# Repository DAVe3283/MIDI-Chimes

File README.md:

# MIDI-Chimes
Software &amp; notes from retrofitting some old chimes to MIDI control

Eventually, this will contain schematics, PCB layouts, data sheets, and source
code to make everything work. I will add things as I get to them.

## Project Details

TODO: writeup project details

## Firmware

The project uses several Teensy 3.2 microcontrollers. There is a master, which
handles MIDI and the user interface. The rest are slaves, which run 10 chimes
each.

The master and slaves communicate over I2C. The master talks to a touch screen
LCD over SPI.

### Libraries

I am using the following libraries:

* [i2c_t3][] - A superior I2C library that runs quite fast on the Teensy3.
* [ILI9341_t3][] - An optimized ILI9343 SPI LCD driver library for the Teensy3.
* [ILI9341_fonts][] - Additional fonts for ILI9341_t3.
* [Adafruit_STMPE610][] - STMPE610 SPI touch screen controller library.
* [Adafruit_FT6206][] - FT6206 I2C touch screen controller library.
* [SdFat][] - SD Card + FAT file system library.
* [IniFile][] - Arduino library to parse INI files.

Some minor changes are needed to make the libraries work together for this
project.

#### Adafruit_STMPE610

The line `#include <Wire.h>` needs changed to `#include <i2c_t3.h>` or it
conflicts with the i2c_t3 library.

#### SdFat

To work right, the SdFat library needs the following settings in SdFatConfig.h:

`#define SD_SPI_CONFIGURATION 1`

This uses the Arduino SPI.h library, which is really an optimized one for the
Teensy 3.1.

`#define ENABLE_SPI_TRANSACTION 1`

This enables SPI transactions, which makes using multiple devices on the SPI bus
much nicer.

I had some issues with SdFat-beta, but I might go back and make that work,
because it does some cool stuff.

#### IniFile

In IniFile.h, `#include <SD.h>` needs changed to `#include <SdFat.h>`.

Immediately below the includes, add the following so the inline code works with
this program:

```c++
extern SdFat sd;
#define SD sd
```

## Schematics

See the "PCB & Schematic" directory, and the [PCB.md](Notes/PCB.md) file.

## License

Content in each folder may be licensed differently. Overall, I strive to use the
Unlicense, but some portions may use external libraries preventing that. Those
portions will be licensed as necessary. Data sheets and the like are provided
for reference only, and are subject to all licenses/copyright specified within.

[Adafruit_FT6206]: https://github.com/adafruit/Adafruit_FT6206_Library
[Adafruit_STMPE610]: https://github.com/adafruit/Adafruit_STMPE610
[i2c_t3]: https://github.com/nox771/i2c_t3
[ILI9341_fonts]: https://github.com/PaulStoffregen/ILI9341_fonts
[ILI9341_t3]: https://github.com/PaulStoffregen/ILI9341_t3
[SdFat]: https://github.com/greiman/SdFat
[IniFile]: https://github.com/stevemarple/IniFile

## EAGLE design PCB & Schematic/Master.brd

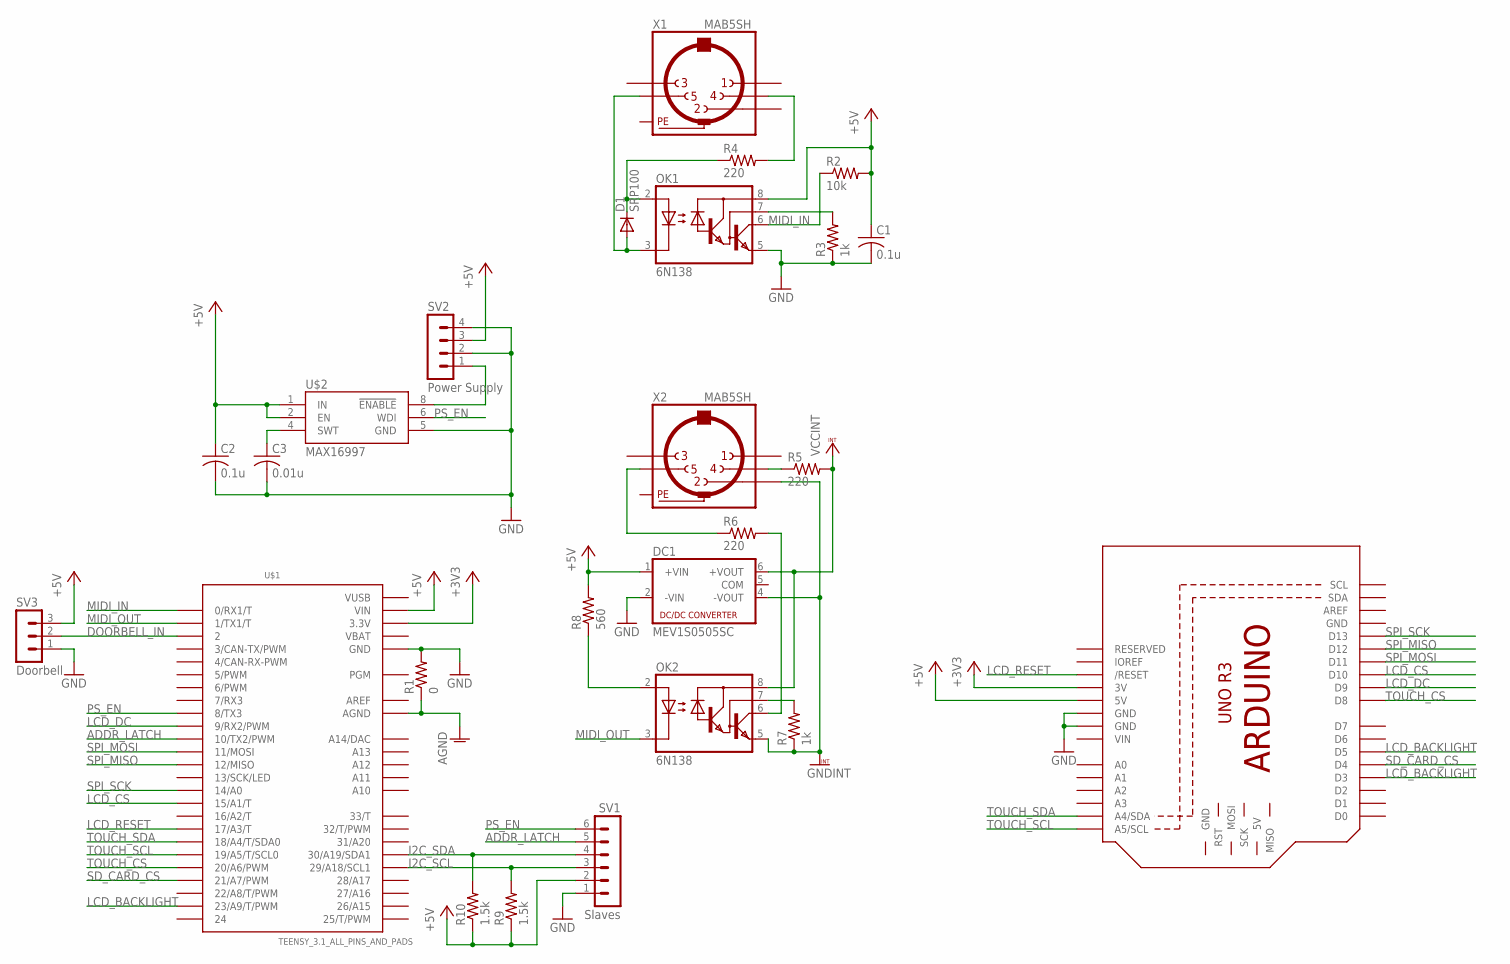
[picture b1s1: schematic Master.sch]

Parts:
C1, C2: 0.1u; C0805
C3: 0.01u; C0805
D1: SRP100; DO41-10
DC1: MEV1S0505SC; NMA
M1: ARDUINO_R3_ICSP_NODIM; ARDUINOR3_ICSP_NODIM
OK1, OK2: 6N138; DIL08
R1: 0; R0805
R2: 10k; R0805
R3, R7: 1k; R0805
R4, R5, R6: 220; R0805
R8: 560; R0805
R9, R10: 1.5k; R0805
SV1: Slaves; MA06-1
SV2: Power Supply; MA04-1
SV3: Doorbell; MA03-1
U$1: TEENSY_3.1_ALL_PINS_AND_PADS; TEENSY3_ALL_PINS_&_PADS
U$2: MAX16997; UMAX-U8-1
X1, X2: MAB5SH

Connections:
+3V3: M1.3V, U$1.3.3V, U$1.3.3V1 (3.3V), U$1.3.3V2 (3.3V)
+5V: C1.1, C2.1, DC1.1 (+VIN), M1.5V, OK1.8 (VCC), R2.2, R8.2, R9.1, R10.1, SV1.2, SV2.3, SV3.3, U$1.VIN, U$2.1 (IN), U$2.2 (EN)
ADDR_LATCH: SV1.5, U$1.10 (10/TX2/PWM)
AGND: R1.1, U$1.AGND
AREF: U$1.AREF
DOORBELL_IN: SV3.2, U$1.2
GND: C1.2, C2.2, C3.2, DC1.2 (-VIN), M1.GND, M1.GND@1 (GND), M1.GND@3 (GND), OK1.5 (GND), R1.2, R3.1, SV1.1, SV2.2, SV2.4, SV3.1, U$1.GND, U$1.GND1 (GND), U$1.GND2 (GND), U$2.5 (GND)
GNDINT: DC1.4 (-VOUT), OK2.5 (GND), R7.1, X2.2
I2C_SCL: R9.2, SV1.3, U$1.29 (29/A18/SCL1)
I2C_SDA: R10.2, SV1.4, U$1.30 (30/A19/SDA1)
LCD_BACKLIGHT: M1.D3, M1.D5, U$1.23/A9 (23/A9/T/PWM)
LCD_CS: M1.D10, U$1.15/A1 (15/A1/T)
LCD_DC: M1.D9, U$1.9 (9/RX2/PWM)
LCD_RESET: M1.RESET (/RESET), U$1.17/A3 (17/A3/T)
MIDI_IN: OK1.6 (VO), R2.1, U$1.0 (0/RX1/T)
MIDI_OUT: OK2.3 (C), U$1.1 (1/TX1/T)
unnamed: R6.1, X2.5
unnamed: OK1.7 (VB), R3.2
unnamed: D1.C, OK1.2 (A), R4.1
unnamed: R4.2, X1.4
unnamed: D1.A, OK1.3 (C), X1.5
unnamed: OK2.6 (VO), R6.2
unnamed: R5.1, X2.4
unnamed: C3.1, U$2.4 (SWT)
unnamed: OK2.2 (A), R8.1
unnamed: OK2.7 (VB), R7.2
unnamed: SV2.1, U$2.8 (!ENABLE)
PE: X1.PE, X1.PE@ (PE), X2.PE, X2.PE@ (PE)
PS_EN: SV1.6, U$1.8 (8/TX3), U$2.6 (WDI)
SD_CARD_CS: M1.D4, U$1.21/A7 (21/A7/PWM)
SPI_MISO: M1.D12, U$1.12 (12/MISO)
SPI_MOSI: M1.D11, U$1.11 (11/MOSI)
SPI_SCK: M1.D13, U$1.14/A0
TOUCH_CS: M1.D8, U$1.20/A6 (20/A6/PWM)
TOUCH_SCL: M1.A5 (A5/SCL), U$1.19/A5 (19/A5/T/SCL0)
TOUCH_SDA: M1.A4 (A4/SDA), U$1.18/A4 (18/A4/T/SDA0)
VBAT: U$1.VBAT
VCCINT: DC1.6 (+VOUT), OK2.8 (VCC), R5.2
VIN: M1.VIN
VUSB: U$1.VUSB

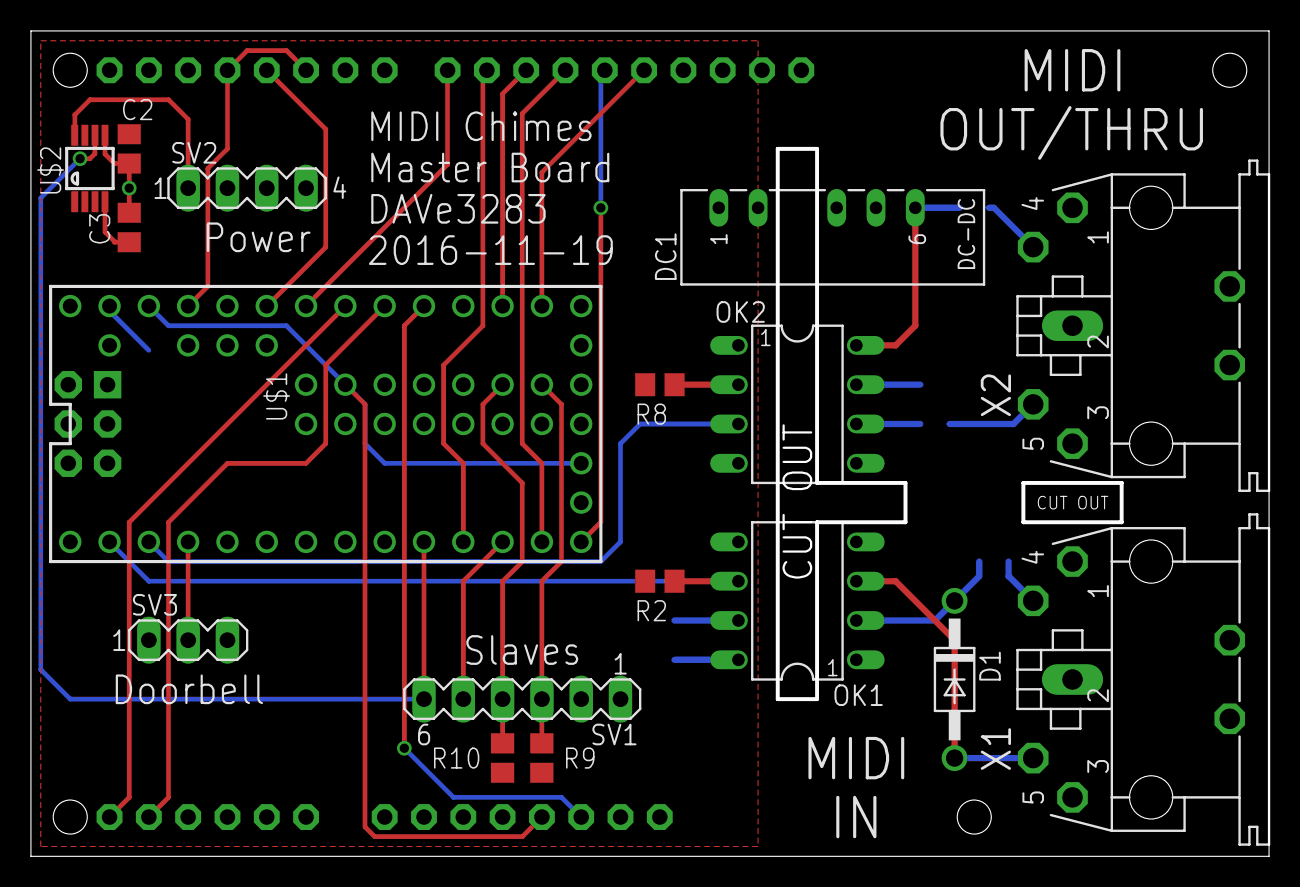
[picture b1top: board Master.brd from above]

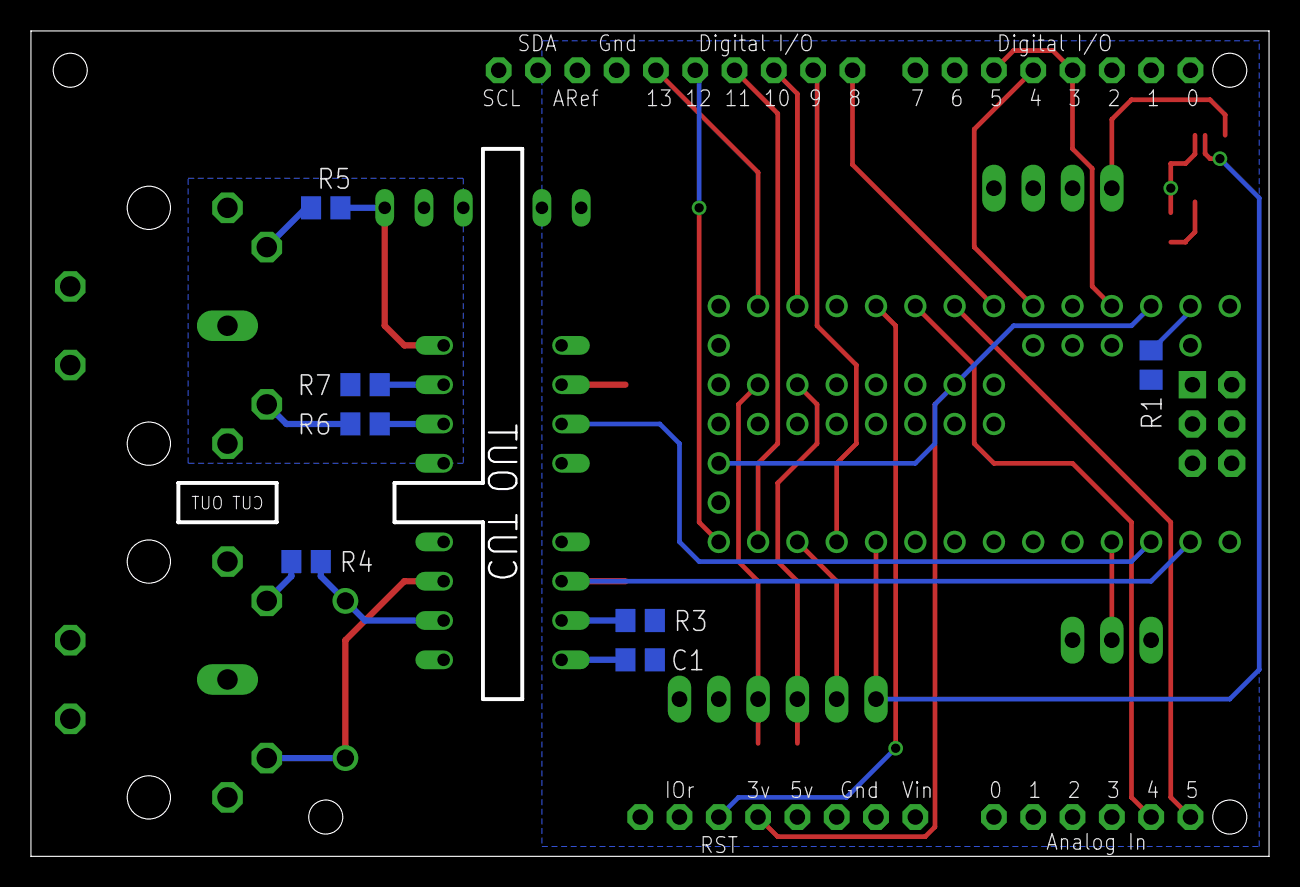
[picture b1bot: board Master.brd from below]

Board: 2 copper layers, 79.8 x 53.1 mm, 25 parts (8 on the bottom side), 36 nets.

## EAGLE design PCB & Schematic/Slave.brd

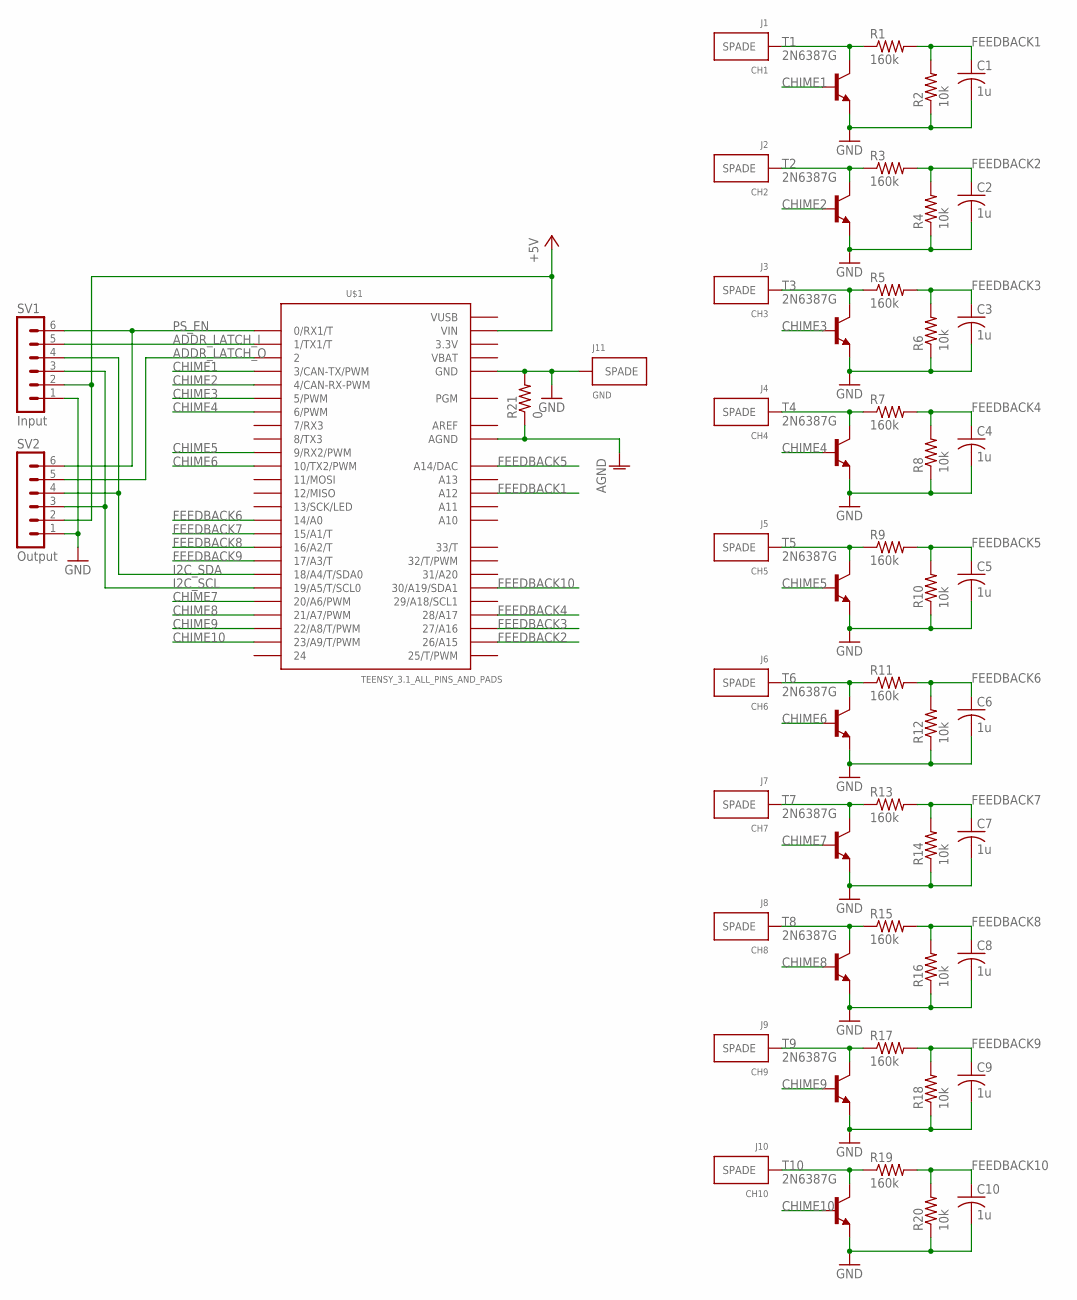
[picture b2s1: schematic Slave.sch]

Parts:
C1, C2, C3, C4, C5, C6, C7, C8, C9, C10: 1u; C0805
J1: CH1; 19705-4001
J2: CH2; 19705-4001
J3: CH3; 19705-4001
J4: CH4; 19705-4001
J5: CH5; 19705-4001
J6: CH6; 19705-4001
J7: CH7; 19705-4001
J8: CH8; 19705-4001
J9: CH9; 19705-4001
J10: CH10; 19705-4001
J11: GND; 19705-4001
R1, R3, R5, R7, R9, R11, R13, R15, R17, R19: 160k; R0805
R2, R4, R6, R8, R10, R12, R14, R16, R18, R20: 10k; R0805
R21: 0; R0805
SV1: Input; MA06-1
SV2: Output; MA06-1
T1, T2, T3, T4, T5, T6, T7, T8, T9, T10: 2N6387G; TO220V
U$1: TEENSY_3.1_ALL_PINS_AND_PADS; TEENSY3_ALL_PINS_&_PADS

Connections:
3.3V: U$1.3.3V, U$1.3.3V1 (3.3V), U$1.3.3V2 (3.3V)
+5V: SV1.2, SV2.2, U$1.VIN
ADDR_LATCH_I: SV1.5, U$1.1 (1/TX1/T)
ADDR_LATCH_O: SV2.5, U$1.2
AGND: R21.1, U$1.AGND
AREF: U$1.AREF
CHIME1: T1.1 (B), U$1.3 (3/CAN-TX/PWM)
CHIME2: T2.1 (B), U$1.4 (4/CAN-RX-PWM)
CHIME3: T3.1 (B), U$1.5 (5/PWM)
CHIME4: T4.1 (B), U$1.6 (6/PWM)
CHIME5: T5.1 (B), U$1.9 (9/RX2/PWM)
CHIME6: T6.1 (B), U$1.10 (10/TX2/PWM)
CHIME7: T7.1 (B), U$1.20/A6 (20/A6/PWM)
CHIME8: T8.1 (B), U$1.21/A7 (21/A7/PWM)
CHIME9: T9.1 (B), U$1.22/A8 (22/A8/T/PWM)
CHIME10: T10.1 (B), U$1.23/A9 (23/A9/T/PWM)
FEEDBACK1: C1.1, R1.2, R2.2, U$1.A12
FEEDBACK2: C2.1, R3.2, R4.2, U$1.26 (26/A15)
FEEDBACK3: C3.1, R5.2, R6.2, U$1.27 (27/A16)
FEEDBACK4: C4.1, R7.2, R8.2, U$1.28 (28/A17)
FEEDBACK5: C5.1, R9.2, R10.2, U$1.RESET/DAC (A14/DAC)
FEEDBACK6: C6.1, R11.2, R12.2, U$1.14/A0
FEEDBACK7: C7.1, R13.2, R14.2, U$1.15/A1 (15/A1/T)
FEEDBACK8: C8.1, R15.2, R16.2, U$1.16/A2 (16/A2/T)
FEEDBACK9: C9.1, R17.2, R18.2, U$1.17/A3 (17/A3/T)
FEEDBACK10: C10.1, R19.2, R20.2, U$1.30 (30/A19/SDA1)
GND: C1.2, C2.2, C3.2, C4.2, C5.2, C6.2, C7.2, C8.2, C9.2, C10.2, J11.P$1, J11.P$2, R2.1, R4.1, R6.1, R8.1, R10.1, R12.1, R14.1, R16.1, R18.1, R20.1, R21.2, SV1.1, SV2.1, T1.3 (E), T2.3 (E), T3.3 (E), T4.3 (E), T5.3 (E), T6.3 (E), T7.3 (E), T8.3 (E), T9.3 (E), T10.3 (E), U$1.GND, U$1.GND1 (GND), U$1.GND2 (GND)
HS1: J1.P$1, J1.P$2, R1.1, T1.2 (C)
HS2: J2.P$1, J2.P$2, R3.1, T2.2 (C)
HS3: J3.P$1, J3.P$2, R5.1, T3.2 (C)
HS4: J4.P$1, J4.P$2, R7.1, T4.2 (C)
HS5: J5.P$1, J5.P$2, R9.1, T5.2 (C)
HS6: J6.P$1, J6.P$2, R11.1, T6.2 (C)
HS7: J7.P$1, J7.P$2, R13.1, T7.2 (C)
HS8: J8.P$1, J8.P$2, R15.1, T8.2 (C)
HS9: J9.P$1, J9.P$2, R17.1, T9.2 (C)
HS10: J10.P$1, J10.P$2, R19.1, T10.2 (C)
I2C_SCL: SV1.3, SV2.3, U$1.19/A5 (19/A5/T/SCL0)
I2C_SDA: SV1.4, SV2.4, U$1.18/A4 (18/A4/T/SDA0)
PS_EN: SV1.6, SV2.6, U$1.0 (0/RX1/T)
VBAT: U$1.VBAT
VUSB: U$1.VUSB

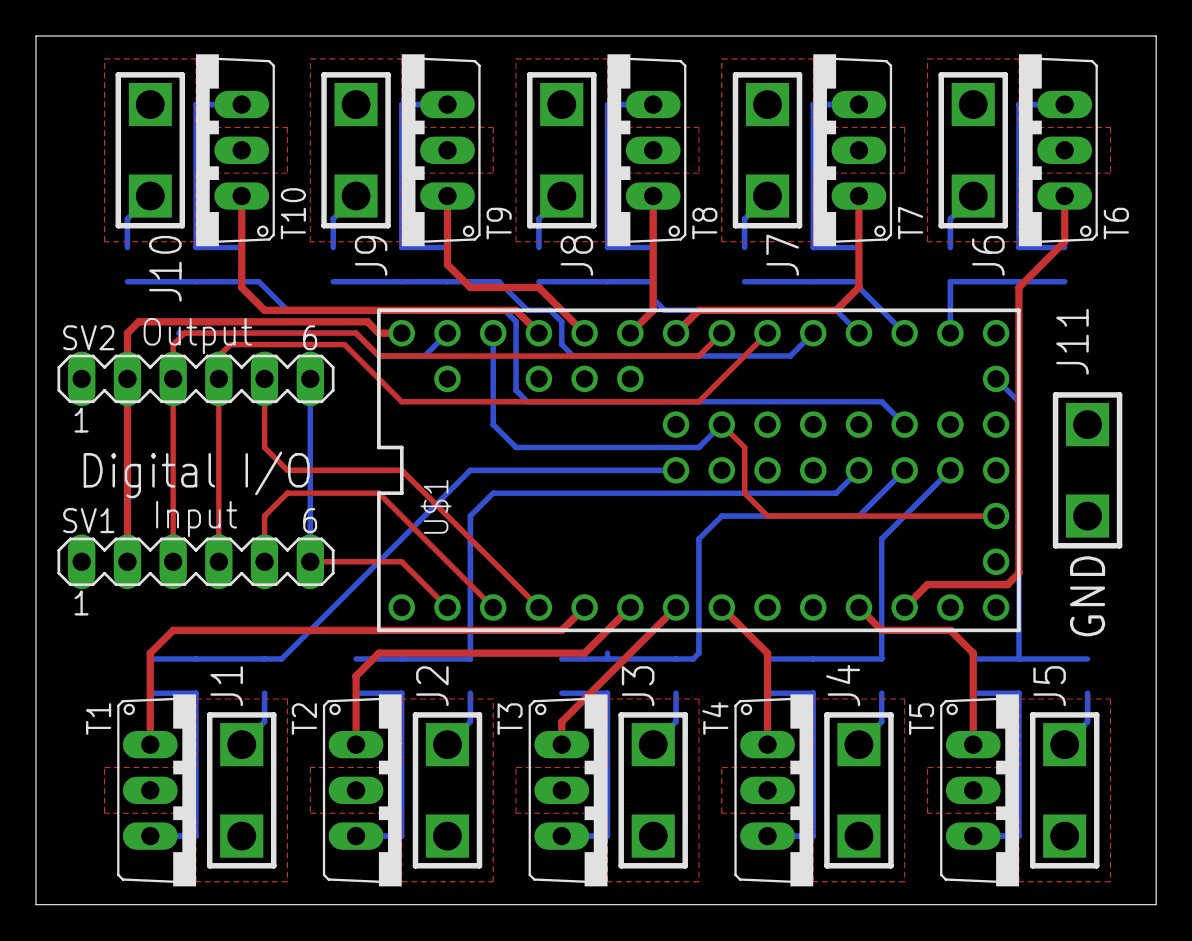
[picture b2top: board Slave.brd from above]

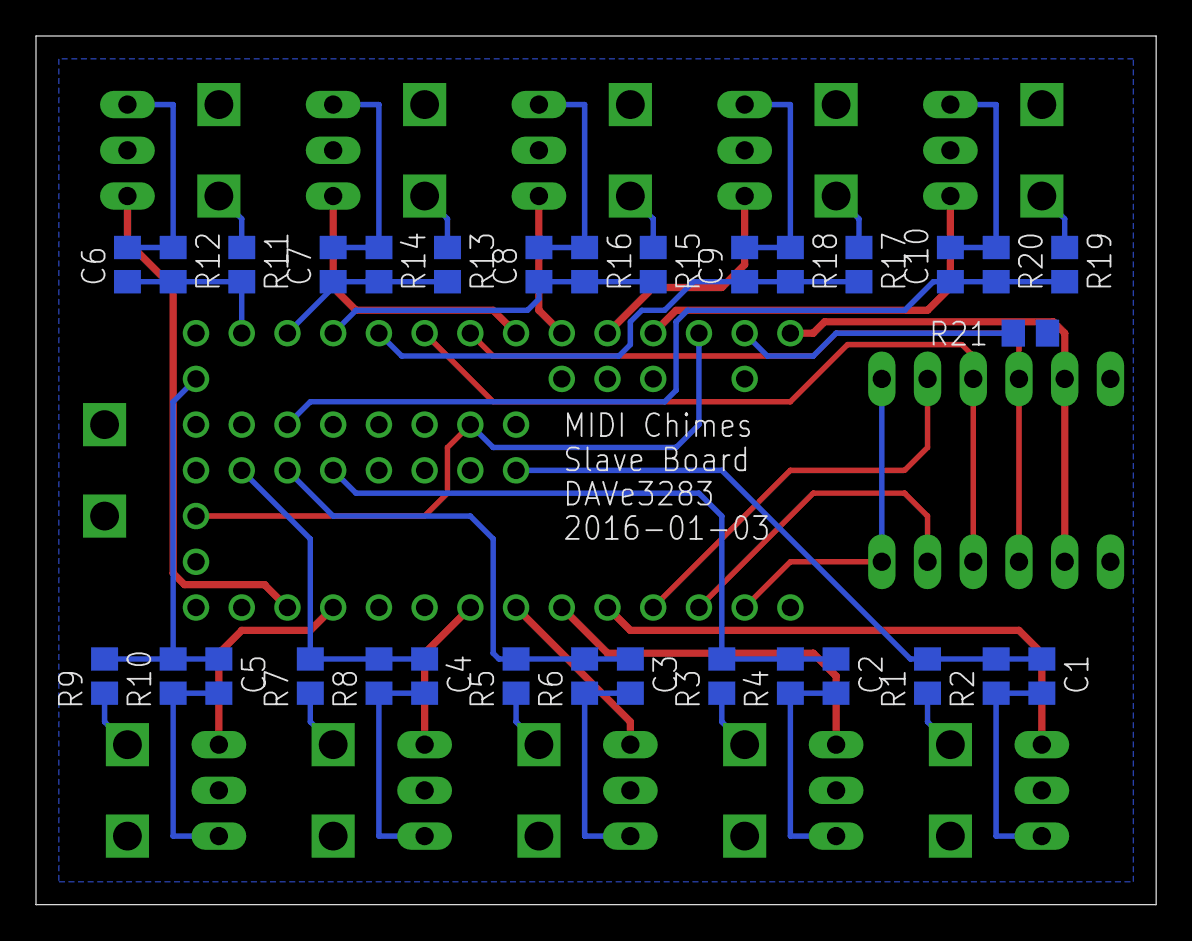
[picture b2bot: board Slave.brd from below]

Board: 2 copper layers, 62.2 x 48.3 mm, 55 parts (31 on the bottom side), 39 nets.

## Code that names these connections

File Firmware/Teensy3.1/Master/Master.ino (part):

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const uint16_t maximum_dc((1 << pwm_bits) - 1);

// Pins
const uint8_t spi_mosi_pin(11);
const uint8_t spi_miso_pin(12);
const uint8_t spi_sck_pin(14);
const uint8_t sd_cs_pin(21);
const uint8_t doorbell_pin(2);
const uint8_t ps_en_pin(8);
const uint8_t addr_latch_pin(10);
const uint8_t led_pin(13);

// Touch Screen
// Pins
const uint8_t lcd_reset_pin(17);
const uint8_t lcd_cs_pin(15);
const uint8_t lcd_dc_pin(9);
const uint8_t touch_cs_pin(20);
// Backlight
const uint8_t lcd_backlight_pin(23);
const uint8_t lcd_bl_pwm_bits(16);
const uint32_t lcd_bl_pwm_freq(549); // Hz
#ifndef CAPACITIVE_TS
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
// Power supply
bool ps_enabled(true); // Is the power supply enabled?
bool ps_en_high(false); // Is the PS_EN pin high currently?

// Backlight
uint16_t backlight_pwm(lcd_bl_pwm_max);
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SdFile dirFile;

// Touch Screen
ILI9341_t3 tft = ILI9341_t3(lcd_cs_pin, lcd_dc_pin, lcd_reset_pin, spi_mosi_pin, spi_sck_pin, spi_miso_pin); // TFT LCD
#ifdef CAPACITIVE_TS
  Adafruit_FT6206 ts = Adafruit_FT6206();  // Using default Arduino I²C pins?
#else
  Adafruit_STMPE610 ts = Adafruit_STMPE610(touch_cs_pin); // Touch sensor
#endif

// µGUI
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  pinMode(led_pin, OUTPUT);

  // Configure address latch pin
  pinMode(addr_latch_pin, OUTPUT);
  digitalWrite(addr_latch_pin, LOW);

  // Configure PS_EN
  pinMode(ps_en_pin, OUTPUT);
  digitalWrite(ps_en_pin, LOW);
  ps_en_high = false;

  // Configure doorbell
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  attachInterrupt(digitalPinToInterrupt(doorbell_pin), doorbell_isr, RISING);

  // Configure LCD backlight
  pinMode(lcd_backlight_pin, OUTPUT);
  analogWriteResolution(lcd_bl_pwm_bits);
  analogWriteFrequency(lcd_backlight_pin, lcd_bl_pwm_freq);
  analogWrite(lcd_backlight_pin, backlight_pwm);

  // Configure TFT
  tft.begin();
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  Wire1.endTransmission(I2C_STOP, 300);

  // Latch address
  digitalWrite(addr_latch_pin, HIGH);
  delayMicroseconds(slave_latch_delay);
  digitalWrite(addr_latch_pin, LOW);

  // Check for ACK
  bool gotSlave(i2c_check_ack(slave_address++));
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    }

    // Write to the pin
    digitalWrite(ps_en_pin, ps_en_high ? HIGH : LOW);
  }
}

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  {
    backlight_pwm = new_val;
  }
  analogWrite(lcd_backlight_pin, backlight_pwm);
  return true;
}
bool backlight_down()
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  {
    backlight_pwm = new_val;
  }
  analogWrite(lcd_backlight_pin, backlight_pwm);
  return true;
}

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
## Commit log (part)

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2015-08-30 Initial project structure, README, and test code.
    Includes a very simple firmware to test PWM on the Teensy,
    allowing me to determing PWM parameters that work well on
    the chimes with the transistors I have.
2015-08-30 Add notes on PIC pin usage.
    Fix typo in README.
2015-08-31 Figure out PWM settings, add notes.
2015-08-31 Add skeleton code for PIC16F1503 firmware.
2015-10-25 Add ignore files and update notes for MPLAB.X solution.
2016-01-22 Switch to using all Teensys due to time constraints.
    Also because MPLABX sucks.
2016-01-22 Create a skeleton master firmware.
2016-01-23 Fix formatting derp with a code block.
2016-01-25 Switch from 10 channels per slave to 9 channels per slave.
    This lets me use the analog inputs to verify the transistors
    are working as expected, measure power supply voltage, etc.
2016-01-31 Added initial PCB layout using Eagle.
    It passes design rule checks, but I should still go over
    it once more by hand to sanity check everything.
2016-02-06 Update Slave firmware to match schematic.
    I ended up changing around the feedback inputs to clean up the
    PCB layout.
2016-02-13 Begin work on handling feedback to verify transistor operation.
    Address potential race conditions / critical sections.
    This might increase latency slightly, but should prevent a number of bugs.
    Make USB debug output off by default.
    I may eventually remove it entirely from the production firmware (#define?).
2016-02-14 Add description to Eagle project.
2016-02-15 Remove i2c_t3 library local copy.
    It has been moved to my libraries folder so I can reference it from
    other libraries (like the display libraries I will use soon).
2016-02-15 Update README with project changes / progress.
2016-02-16 Add support for FT6206 capacitive touchscreen driver.
2016-02-16 Fix for I2C Capacitive touchscreen
    Problem was physical hookup issues.
2016-02-26 Initial SD card tests.
    Just read some SD card info and a quick file list to ensure the SD
    card works.
2016-02-26 Initial GUI tests.
    There is a problem with touch events. It responds to the
    _previous_ touch event, for some reason. I might be doing
    something wrong.
    Hardware acceleration appears to be working. I could tweak the
    ILI9341_t3 library and make it even faster, if I cared.
2016-02-26 Fix µGUI "click" event to actually fire.
    It works as expected for buttons. Checkboxes are untested.
2016-02-27 Start converting things to µGUI.
    Master volume is working again, but doesn't look as good.
    There is much more to do...
2016-02-27 Debug some SPI weirdness, improve volume buttons.
    The big problem was the SdFat-beta library. It was causing _both_
    hardware SPI clock pins to run, and limiting the frequency of
    everything to 100 kHz.
    Switching to SdFat (non-beta) and tweaking the settings got things
    working right.
2016-02-28 Switch images to a naïve RLE compression.
    This saves a lot of program space. I think I can still pull the
    trick of mirroring the :( emoticon to save even more space.
2016-02-28 Switch RLE image storage from uint16_t to uint8_t.
    This saves a bit of program memory. I think this is about as small
    as I can make these images without implementing a real compression
    algorithm.
2016-02-28 Add support for transparent text background
    If text is rendered with the same background and foreground color, the background
    rendering is now skipped. This results in rendering text on a "transparent" background.
2016-02-28 Fix encoding issue in the hacky codepage hack.
    Not only was the hack hacky, but the encoding of the C file was
    sketchy. So much sketch.
2016-02-28 Revert transparency work on 8bpp fonts.
    We don't think this will actually work, and we don't use it.
    Better to leave alone.
2016-02-28 Refactor settings window
    Moved all settings window related stuff into its own functions.
    Also renamed all UI objects to have useful names.
2016-02-28 Volume bar uses a larger font.
    Also tweaked global variables to use less memory.
2016-02-29 Initial round of logic for file browse dialog
    Converted file list from one textbox to several. This dramatically simplifies
    the highlight logic. This dialog is currently populated by debug text.
2016-02-29 Add initial backlight dimming support.
    No UI yet.
2016-02-29 Quick hack to fix BSOD.
    It lists some files, so I'm calling it a night.
2016-02-29 File browser can now traverse up the tree
2016-03-03 Cleanup some file browser edge cases.
    Scrolling was odd at the top & bottom of the display for me, and
    a few other minor bugs.
    Also saved a bunch of RAM:
    - Icon buffer didn't need to be 256 characters long per entry.
    - It actually didn't need to be a buffer at all. Just a pointer to
    the icon.
2016-03-03 Actually commit the right file. D'oh!
2016-03-04 Initial MIDI program (instrument) support.
    See Notes/MIDI.md for more.
2016-03-04 Begin PCB for the master. Missing key features!
    It is missing the power supply connector, among other things.
2016-03-05 Make the correct part for the watchdog.
    This is much cleaner.
2016-03-06 Sort file browser entries
    The QueueList sorting modifications should work for any QueueList, but
    have only been tested with the FileInfo struct.
    The FileInfo sort order is not ideal, but it is passable. Numbers come
    before letters, and letters are treated as case insensitive. It will
    still have trouble with numerical series, meaning (1, 2, 20, 10) will
    become (1, 10, 2, 20).
2016-03-06 Cleanup edge cases
    Forcing null terminators, since it turns out that `strncpy` does
    not guarantee a null terminator.
2016-03-08 Power connector now 4 pin. Add doorbell notes.
    The 6 pin connector was unnecessary, and risked confusion with the
    slave board connector.
    Added some notes on the cheap wireless doorbell I bought to
    integrate with the chimes.
2016-03-12 Update Master PCB with correct cutout method.
    OSH Park recommends this method to ensure the cutout is done.
    Added pin definition in firmware for the doorbell input to match PCB.
2016-03-12 Doorbell test
    I want to make sure the doorbell doesn't communicate with the I2C
    EEPROM at random. It appears to only communicate when the button is
    pressed, which would be perfect.
2016-03-25 Additional notes for MIDI compatibility & plans.
    Added the manual for the Monoprice keyboard, as well as some notes
    on MIDI commands/messages, and some testing on the slave board.
2016-04-08 Remove PIC16F1503 firmware & docs.
    I didn't end up using it.
2016-04-09 Fix checkboxes in µGUI somewhat.
    Added a couple test options to the settings screen.
    I really need to map out what I want for options, and rewrite the
    whole settings screen.
2016-04-09 Fix BSOD bitmaps.
    They were missing the last run due to a bug in the program I wrote
    to convert them. This happened to work out fine, but doesn't if I
    decompress them to an array and send the array as one operation.
2016-04-09 Increase BSOD drawing speed another 25%!
    This is nearly 60% faster than the original method!
    However, it uses a LOT of memory (23k), and might not be reliable.
    So into a branch it goes.
2016-04-10 Begin work moving settings into a config file.
    The file will be loaded at startup.
2016-04-10 Read note map from Settings.ini on SD card!
2016-04-10 Add calibration support to settings file.
2016-04-23 Refactoring to clean up code.
    Makes the logic in the slave firmware more clear.
2016-04-23 Fix overflow causing a missed strike request.
    It was possible that if a strike command was recieved 49.7 days
    (specifically, 4294967295 to 4294967455 ms) after the last strike
    was completed on that channel, the new strike command would be
    ignored.
    This is now fixed.
2016-04-23 Finding some strange behavior here...
    It appears ps_stable_timer is initially evaluating as > ps_toggle_time,
    but later on when I checked again, it isn't anymore.
    I need to see why that is.
2016-04-23 Switched timeout from microseconds to milliseconds.
    This avoids the problem of micros() going backwards, but I would
    still like to get to the bottom of that one at some point.
2016-04-26 Initial work toward a slave POST.
2016-04-30 Update settings with physical connections.
    This is how I believe the chimes are going to be hung from the frame.
2016-04-30 Fix master volume not working.
    Also cleanup some coding conventions and remove some commented out code.
2016-04-30 Slave firmware is feature-complete!
    This should be stable enough for an initial release.
    Note: the reason the allowed error is so hihg (20%) is because one
    of my coils appears to have some damage (internal shorts) and is
    ~15% out from the rest. So for now, I just allow it, but I might
    repair/replace the damaged coil and tighten up the allowed error.
    The rest of the coils are within 1% of expected from what I see.
2016-05-01 Adjust I²C timeouts to allow it to work at 100 kHz.
    It seems to work fine at 1000 kHz, but better to set the timeouts
    appropriately so it will still work if there is a need to slow it
    down in the future.
2016-05-01 Implement 2-point calibration for chimes.
    Now both the minimum and the maximum PWM DC % can be set per channel.
2016-05-01 Periodically check slaves for malfunctions.
    This lets us report the failure, instead of blissfylly carrying on after
    a slave has disabled the power supply, or at least started ignoring
    commands to a damaged channel.
2016-05-01 Additional diagnostic tools for slaves.
    You can now force a failure on Channel 1 for the slave for testing.
2016-05-01 Handle MIDI Control Change Volume message!
    Volume can now be set over MIDI through the Control Change message.
2016-05-02 Implement Master Volume support & fix lots of bugs.
    Calibration now works right, fixes hang on I2C bus errors, etc.
2016-05-04 Fix Master PCB mount.
    I had failed to mirror-image the standoffs, since the board mounts
    upside down compared to the model. D'oh!
2016-05-05 Add clip mounts for Slave PCBs.
    Each slave uses 2 of these clips, rotated 180° from each other.
2016-05-05 Handle Master Volume SysEx message from USB.
    Now handles the Master Volume message from USB as well as the physical
    MIDI port. (In theory, I have not tested it, since I lack the software
    to send a SysEx message over USB.)
2016-06-18 Add notes for re-winding a burnt coil.
2016-11-18 Limit simultaneous chime strikes.
    This prevents overloading the power supply.
2016-11-20 Listen for tubular bells on all channels.
    This makes a whole lot more MIDI files work, and honestly just makes
    more sense. I can/should still add a GUI option to select just one
    channel if the use case calls for it.
2016-11-20 Enable text boxes to be clicked.
2016-11-20 Remove file browser, add about dialog.
    Playing a MIDI file off the SD card is a long-term plan. I will restore
    the code when I get MIDI file playback working.
